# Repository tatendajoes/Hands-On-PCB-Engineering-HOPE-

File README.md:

# USB Charger PCB
**Mentor:** Nehemiah Edison  
**Mentee:** Tatenda Joseph

## Overview
The project focuses on designing and developing a USB charger PCB. The primary function is to provide a regulated 5 V DC supply to charge USB devices (smartphones, tablets, etc.).

## How It Works
1. **12 V DC Input**: Accepts 12 V DC from a car battery, bench supply, or external adapter.  
2. **5 V Buck Conversion (LM73606)**: Synchronous step-down converter steps 12 V down to a regulated 5 V rail (up to 6 A).  
3. **USB Charging Port Controllers (TPS2549 × 2)**: Each USB-A port uses a TPS2549 for BC1.2 signature detection (SDP/CDP/DCP), allowing up to 1.5 A per port.  
4. **Dual-Port Output**: Each port supplies 5 V at 1.5 A (7.5 W), with both ports up to 3 A total (15 W).

## Components
- Capacitors (various values) – 19 total  
- LEDs (BLUE CLEAR SMD R/A) – 2  
- USB Connectors – 2  
- Inductor (Iron-core) – 1  
- Resistors (various values and types) – 13 total  
- LM73606 switching regulator IC – 1  
- TPS2549 IC (BC1.2 port controller) – 2

## Use Cases
- Charging smartphones and tablets (BC1.2-compliant devices, up to 1.5 A)  
- Powering USB modules (Arduinos, ESP32, Raspberry Pi Zero, sensors)  
- Converting 12 V to 5 V for bench or automotive applications

## Objectives
- Design schematic in KiCad and assign footprints  
- Run ERC and complete PCB layout  
- Run DRC and generate Gerbers  
- Create BOM and submit to Oshpark  
- Order parts from DigiKey and assemble PCB  
- Test and validate performance

## Schematic

- Schematic Diagram

- PCB Diagram

## Specifications
| Parameter             | Specification                 |
|-----------------------|-------------------------------|
| **Input**             |                               |
| Voltage range         | 9 – 18 V DC                   |
| Maximum input current | 4 A (at Vin under full load)  |
| **Power Conversion**  |                               |
| Converter IC          | LM73606                       |
| Typical efficiency    | ~90% at 3 A                   |
| **Output (per port)** |                               |
| Voltage               | 5.00 V ± 1%                   |
| Max current           | 1.5 A                         |
| **Combined output**   |                               |
| Total max current     | 3.0 A                         |
| **Port controller**   |                               |
| Controller IC         | TPS2549 × 2                   |
| BC1.2 signatures      | SDP / CDP / DCP               |
| **Environmental**     |                               |
| Operating temperature | –40 °C to +85 °C              |
| **PCB**               |                               |
| Layers & material     | 2-layer FR-4 (1.6 mm)         |
| Dimensions            | 60 mm × 40 mm (approx.)       |

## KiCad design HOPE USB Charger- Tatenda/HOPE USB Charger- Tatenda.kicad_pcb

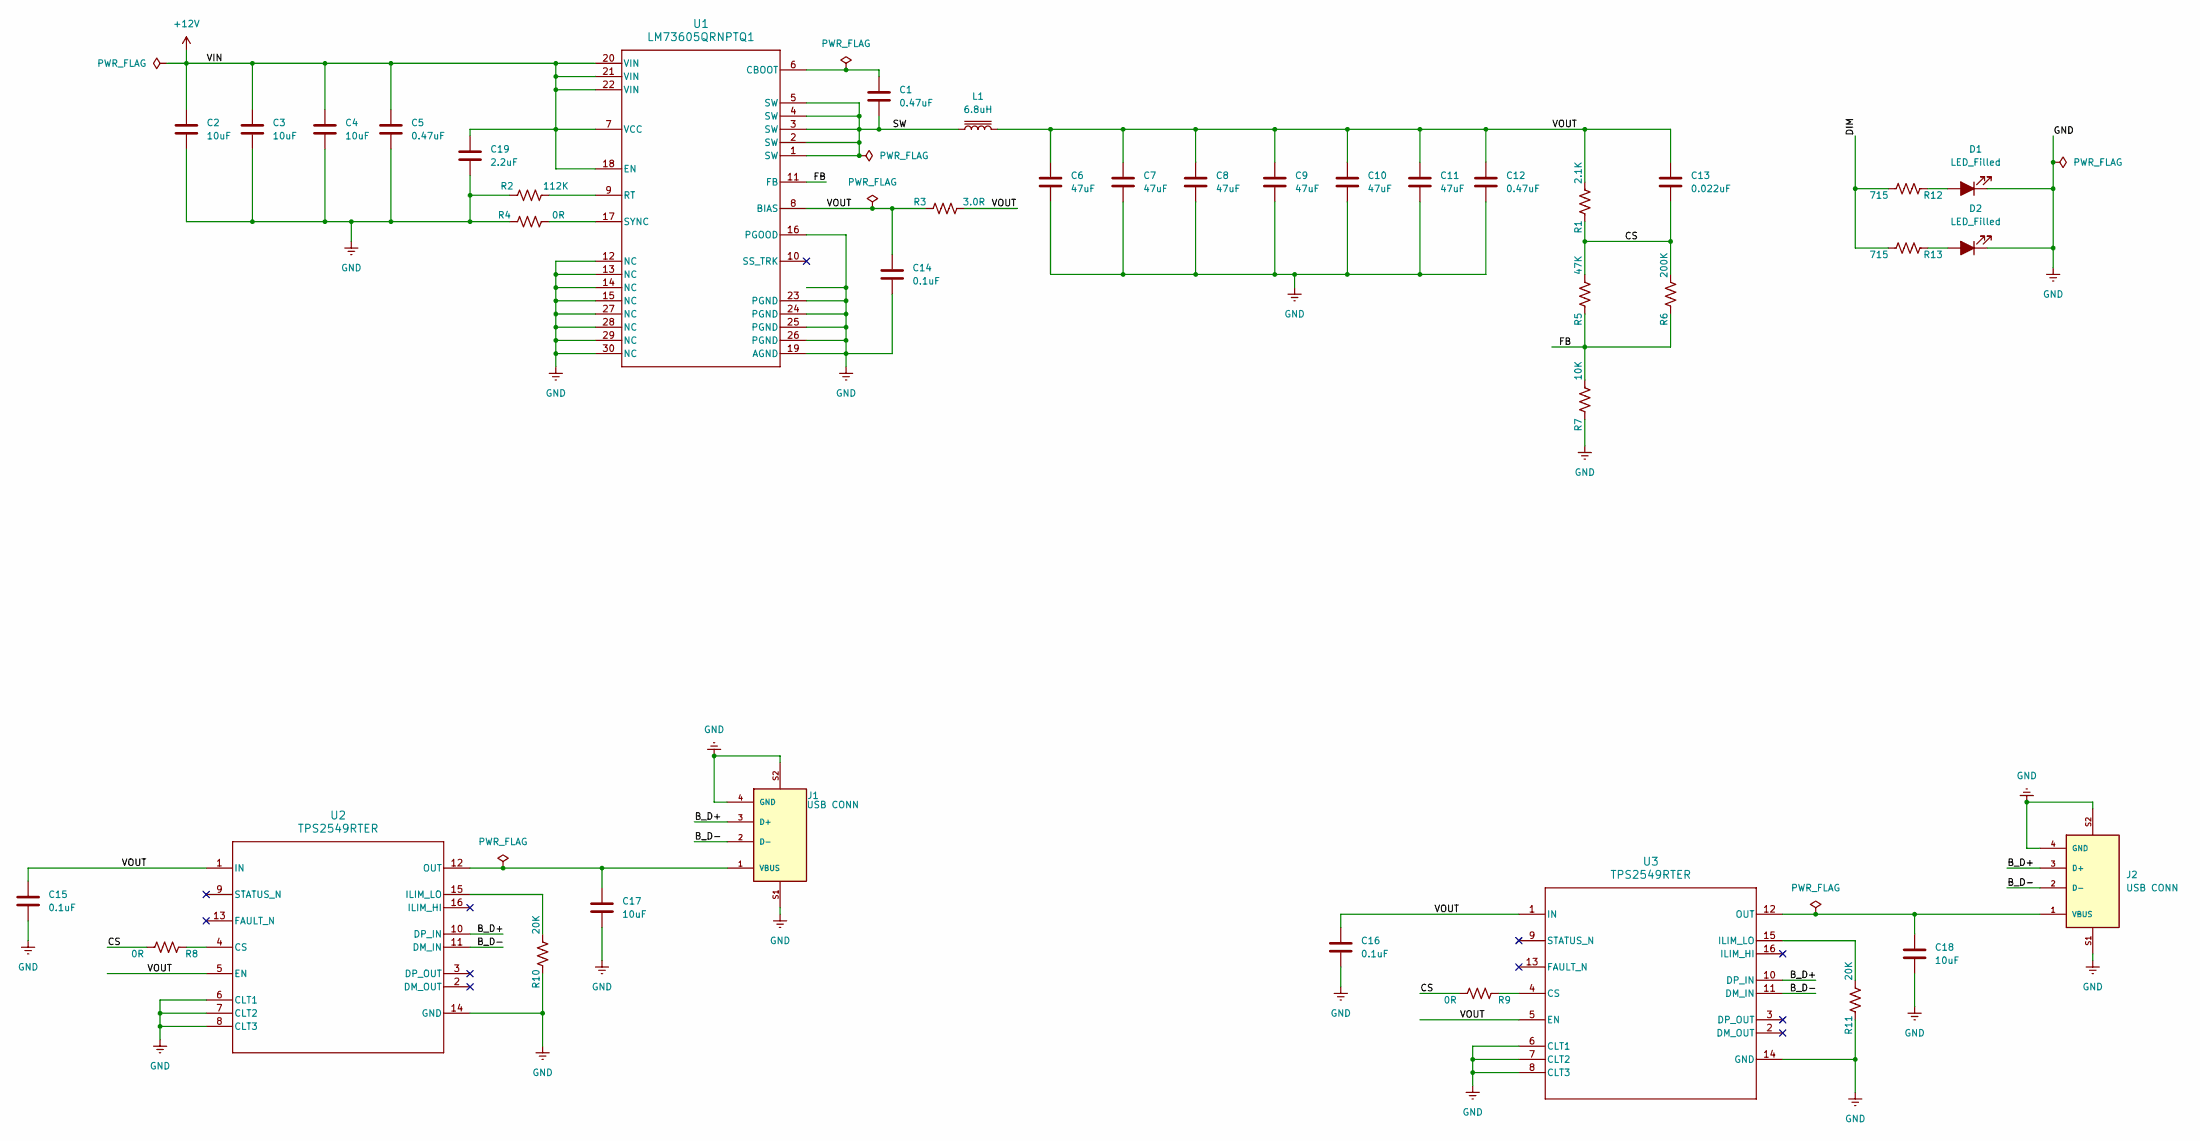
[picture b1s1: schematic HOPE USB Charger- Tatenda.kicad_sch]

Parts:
C1, C5, C12: 0.47uF; C_0603_1608Metric_Pad1.08x0.95mm_HandSolder
C2, C3, C4, C17, C18: 10uF; C_0603_1608Metric_Pad1.08x0.95mm_HandSolder
C6, C7, C8, C9, C10, C11: 47uF; C_0603_1608Metric_Pad1.08x0.95mm_HandSolder
C13: 0.022uF; C_0603_1608Metric_Pad1.08x0.95mm_HandSolder
C14, C15, C16: 0.1uF; C_0603_1608Metric_Pad1.08x0.95mm_HandSolder
C19: 2.2uF; C_0603_1608Metric_Pad1.08x0.95mm_HandSolder
D1, D2: LED_Filled; D_0603_1608Metric_Pad1.05x0.95mm_HandSolder
J1, J2: USB CONN; CUI_UJ2-AH-1-SMT; PARTREV 1.01
L1: 6.8uH; L_0603_1608Metric_Pad1.05x0.95mm_HandSolder
R1: 2.1K; R_0603_1608Metric_Pad0.98x0.95mm_HandSolder
R2: 112K; R_0603_1608Metric_Pad0.98x0.95mm_HandSolder
R3: 3.0R; R_0603_1608Metric_Pad0.98x0.95mm_HandSolder
R4, R8, R9: 0R; R_0603_1608Metric_Pad0.98x0.95mm_HandSolder
R5: 47K; R_0603_1608Metric_Pad0.98x0.95mm_HandSolder
R6: 200K; R_0603_1608Metric_Pad0.98x0.95mm_HandSolder
R7: 10K; R_0603_1608Metric_Pad0.98x0.95mm_HandSolder
R10, R11: 20K; R_0603_1608Metric_Pad0.98x0.95mm_HandSolder
R12, R13: 715; R_0603_1608Metric_Pad0.98x0.95mm_HandSolder
U1: LM73605QRNPTQ1; RNP0030A
U2, U3: TPS2549RTER; RTE0016C

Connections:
+12V: C2.1, C3.1, C4.1, C5.1, C19.1, U1.7 (VCC), U1.18 (EN), U1.20 (VIN), U1.21 (VIN), U1.22 (VIN)
/B_D+: J1.3 (D+), J2.3 (D+), U2.10 (DP_IN), U3.10 (DP_IN)
/B_D-: J1.2 (D-), J2.2 (D-), U2.11 (DM_IN), U3.11 (DM_IN)
/CS: C13.2, R1.2, R5.1, R6.1, R8.1, R9.1
/DIM: R12.1, R13.1
/FB: R5.2, R6.2, R7.1, U1.11 (FB)
/SW: C1.2, L1.1, U1.1 (SW), U1.2 (SW), U1.3 (SW), U1.4 (SW), U1.5 (SW)
/VOUT: C6.1, C7.1, C8.1, C9.1, C10.1, C11.1, C12.1, C13.1, C14.1, C15.1, C16.1, L1.2, R1.1, R3.1, R3.2, U1.8 (BIAS), U2.1 (IN), U2.5 (EN), U3.1 (IN), U3.5 (EN)
GND: C2.2, C3.2, C4.2, C5.2, C6.2, C7.2, C8.2, C9.2, C10.2, C11.2, C12.2, C14.2, C15.2, C16.2, C17.2, C18.2, C19.2, D1.1 (K), D2.1 (K), J1.4 (GND), J1.S1, J1.S2, J2.4 (GND), J2.S1, J2.S2, R2.2, R4.2, R7.2, R10.2, R11.2, U1.12 (NC), U1.13 (NC), U1.14 (NC), U1.15 (NC), U1.16 (PGOOD), U1.19 (AGND), U1.23 (PGND), U1.24 (PGND), U1.25 (PGND), U1.26 (PGND), U1.27 (NC), U1.28 (NC), U1.29 (NC), U1.30 (NC), U2.6 (CLT1), U2.7 (CLT2), U2.8 (CLT3), U2.14 (GND), U3.6 (CLT1), U3.7 (CLT2), U3.8 (CLT3), U3.14 (GND)
unnamed: D1.2 (A), R12.2
unnamed: D2.2 (A), R13.2
unnamed: C17.1, J1.1 (VBUS), U2.12 (OUT)
unnamed: C18.1, J2.1 (VBUS), U3.12 (OUT)
unnamed: C1.1, U1.6 (CBOOT)
unnamed: R2.1, U1.9 (RT)
unnamed: R4.1, U1.17 (SYNC)
unnamed: R8.2, U2.4 (CS)
unnamed: R10.1, U2.15 (ILIM_LO)
unnamed: R9.2, U3.4 (CS)
unnamed: R11.1, U3.15 (ILIM_LO)

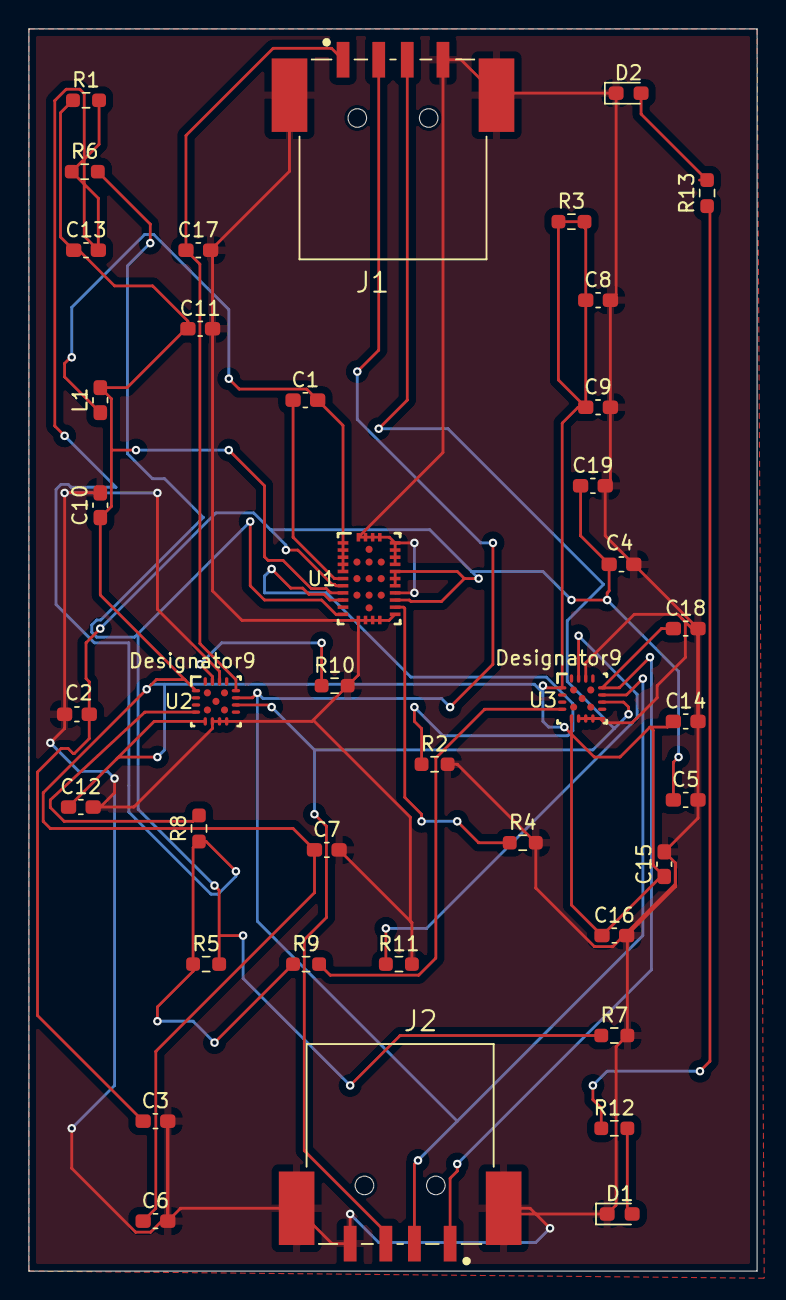
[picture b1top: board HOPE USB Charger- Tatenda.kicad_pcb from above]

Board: 2 copper layers, 51.0 x 87.0 mm, 40 parts (0 on the bottom side), 20 nets.

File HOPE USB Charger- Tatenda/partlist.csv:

"Reference","Value","Datasheet","Footprint","Qty","DNP"
"C1,C5,C12","0.47uF","~","Capacitor_SMD:C_0603_1608Metric_Pad1.08x0.95mm_HandSolder","3",""
"C2,C3,C4,C17,C18","10uF","~","Capacitor_SMD:C_0603_1608Metric_Pad1.08x0.95mm_HandSolder","5",""
"C6,C7,C8,C9,C10,C11","47uF","~","Capacitor_SMD:C_0603_1608Metric_Pad1.08x0.95mm_HandSolder","6",""
"C13","0.022uF","~","Capacitor_SMD:C_0603_1608Metric_Pad1.08x0.95mm_HandSolder","1",""
"C14,C15,C16","0.1uF","~","Capacitor_SMD:C_0603_1608Metric_Pad1.08x0.95mm_HandSolder","3",""
"C19","2.2uF","~","Capacitor_SMD:C_0603_1608Metric_Pad1.08x0.95mm_HandSolder","1",""
"D1,D2","LED_Filled","~","Diode_SMD:D_0603_1608Metric_Pad1.05x0.95mm_HandSolder","2",""
"J1,J2","USB CONN","","Library:CUI_UJ2-AH-1-SMT","2",""
"L1","6.8uH","~","Inductor_SMD:L_0603_1608Metric_Pad1.05x0.95mm_HandSolder","1",""
"R1","2.1K","~","Resistor_SMD:R_0603_1608Metric_Pad0.98x0.95mm_HandSolder","1",""
"R2","112K","~","Resistor_SMD:R_0603_1608Metric_Pad0.98x0.95mm_HandSolder","1",""
"R3","3.0R","~","Resistor_SMD:R_0603_1608Metric_Pad0.98x0.95mm_HandSolder","1",""
"R4,R8,R9","0R","~","Resistor_SMD:R_0603_1608Metric_Pad0.98x0.95mm_HandSolder","3",""
"R5","47K","~","Resistor_SMD:R_0603_1608Metric_Pad0.98x0.95mm_HandSolder","1",""
"R6","200K","~","Resistor_SMD:R_0603_1608Metric_Pad0.98x0.95mm_HandSolder","1",""
"R7","10K","~","Resistor_SMD:R_0603_1608Metric_Pad0.98x0.95mm_HandSolder","1",""
"R10,R11","20K","~","Resistor_SMD:R_0603_1608Metric_Pad0.98x0.95mm_HandSolder","2",""
"R12,R13","715","~","Resistor_SMD:R_0603_1608Metric_Pad0.98x0.95mm_HandSolder","2",""
"U1","LM73605QRNPTQ1","LM73605QRNPTQ1","Library:RNP0030A","1",""
"U2,U3","TPS2549RTER","TPS2549RTER","Library:RTE0016C","2",""

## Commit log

2025-07-05 readme updated
2025-07-05 Add files via upload
    project upload
